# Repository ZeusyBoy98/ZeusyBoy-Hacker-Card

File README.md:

# ZeusyBoy Hacker Card
An NFC business card because it's cool I guess.
Made for Hack Club Fallout

## Zine

## What does it do?
It's a business card which allows me to scan it on any phone and have my website/github appear, and it lights up and LED.

## Why/Motivation?
Because it would seem every other hack clubber has one and they're really cool and could help with industry networking.

## How?
In order to make this project for yourself, you'll need to purchase/3D print the items in the bill of materials below.

| Quantity | Item                     | URL                                                             | Unit Price ($USD) | Total Price ($USD)               |
|----------|--------------------------|-----------------------------------------------------------------|-------------------|----------------------------------|
| 5        | 220nf 25V                | https://jlcpcb.com/partdetail/21832-CL10B224KA8NNNC/C21120      | 0.0075            | 0.04                             |
| 5        | LED Blue 3.1V 5mA 100mcd | https://jlcpcb.com/partdetail/Hubei_KENTOElec-KT0805B/C2293     | 0.0121            | 0.06                             |
| 5        | 47Ω 100mW 75V            | https://jlcpcb.com/partdetail/23909-0603WAF470JT5E/C23182       | 0.0016            | 0.01                             |
| 5        | 3.3V 13.56MHz            | https://jlcpcb.com/partdetail/NxpSemicon-NT3H2111W0FHKH/C710403 | 0.7637            | 3.82                             |
|          | PCBA                     |                                                                 |                   | 26.09(Includes components & PCB) |
|          | Shipping                 |                                                                 |                   | 9.33                             |
| Total    |                          |                                                                 |                   | 35.42                            |

### Build Guide:

#### 1. Preparation<br>
Before starting, make sure you have:
<ul>
<li>The gerbers, pick and place files, and BOM, all available in this repository.
</ul>

#### 2. Ordering
Go to your PCB manufacturer of choice (Make sure they have PCBA) and follow their instructions on how to order, use the zipped gerbers and the bom.csv and positions.csv for the PCB and PCBA (all available in /PCB/production).

#### 3. Firmware
Now you need to initialize the chip:
<ul>
<li>Install an app with the capability to use custom NFC commands, such as NFC Tools IOS or NFC Tools Android. 
<li>Flash the NFC card with this Advanced NFC command, A2:03:E1:10:6D:00,A2:04:03:04:D8:00,A2:05:00:00:FE:00. 
<li>Write any link to the nfc chip
</ul>

Now you can scan this card on a phone and it should open a link to whatever you set it to!
Enjoy your Hacker Card!

## Designing

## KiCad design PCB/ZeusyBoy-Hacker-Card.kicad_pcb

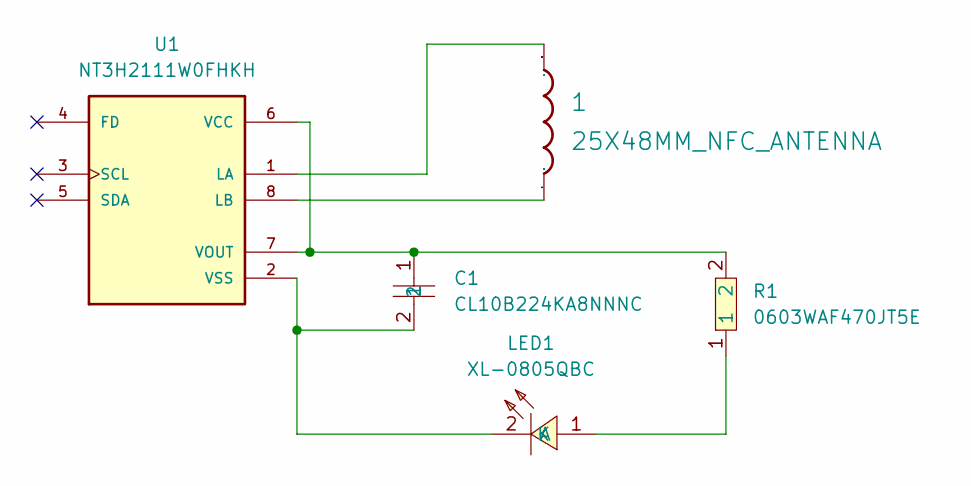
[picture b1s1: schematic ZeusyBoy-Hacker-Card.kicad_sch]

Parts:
1: 25X48MM_NFC_ANTENNA
C1: CL10B224KA8NNNC; 220nf_0603; LCSC Part C21120
LED1: XL-0805QBC; LED0805-RD; LCSC Part C2293
R1: 0603WAF470JT5E; 47_0603; LCSC Part C23182
U1: NT3H2111W0FHKH; QFN8P50_160X160X50L40X20N

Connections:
unnamed: LED1.1 (A), R1.1
unnamed: C1.2, LED1.2 (K), U1.2 (VSS)
unnamed: 1.P$1, U1.1 (LA)
unnamed: 1.P$2, U1.8 (LB)
unnamed: C1.1, R1.2, U1.6 (VCC), U1.7 (VOUT)

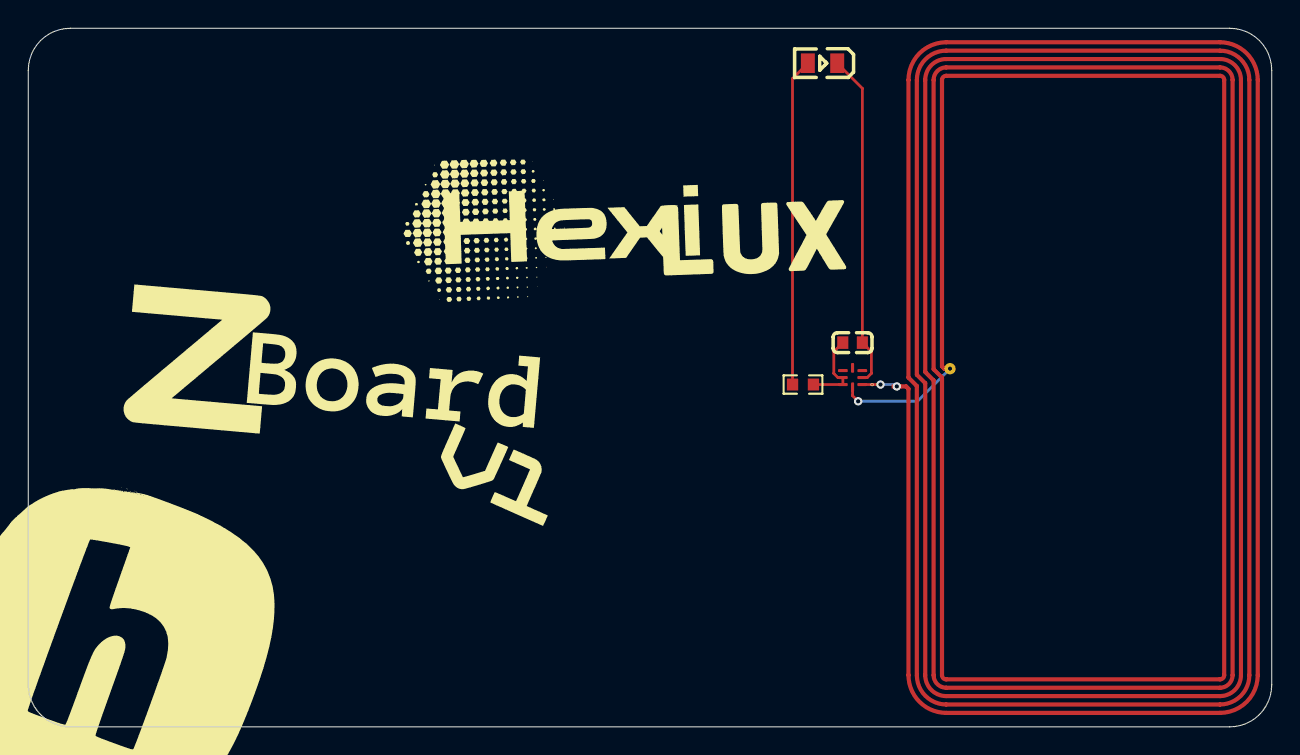
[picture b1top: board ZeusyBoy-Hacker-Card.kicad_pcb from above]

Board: 2 copper layers, 89.0 x 50.0 mm, 5 parts (0 on the bottom side), 5 nets.

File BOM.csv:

Quantity,Item,URL,Unit Price ($USD),Total Price ($USD)
5,220nf 25V,https://jlcpcb.com/partdetail/21832-CL10B224KA8NNNC/C21120,0.0075,0.04
5,LED Blue 3.1V 5mA 100mcd,https://jlcpcb.com/partdetail/Hubei_KENTOElec-KT0805B/C2293,0.0121,0.06
5,47Ω 100mW 75V,https://jlcpcb.com/partdetail/23909-0603WAF470JT5E/C23182,0.0016,0.01
5,3.3V 13.56MHz,https://jlcpcb.com/partdetail/NxpSemicon-NT3H2111W0FHKH/C710403,0.7637,3.82
,PCBA,,,26.09(Includes components & PCB)
,Shipping,,,9.33
Total,,,,35.42

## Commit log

2026-04-25 Rename project to ZeusyBoy Hacker Card
2026-04-26 Add proper README
2026-04-26 Add Zine
